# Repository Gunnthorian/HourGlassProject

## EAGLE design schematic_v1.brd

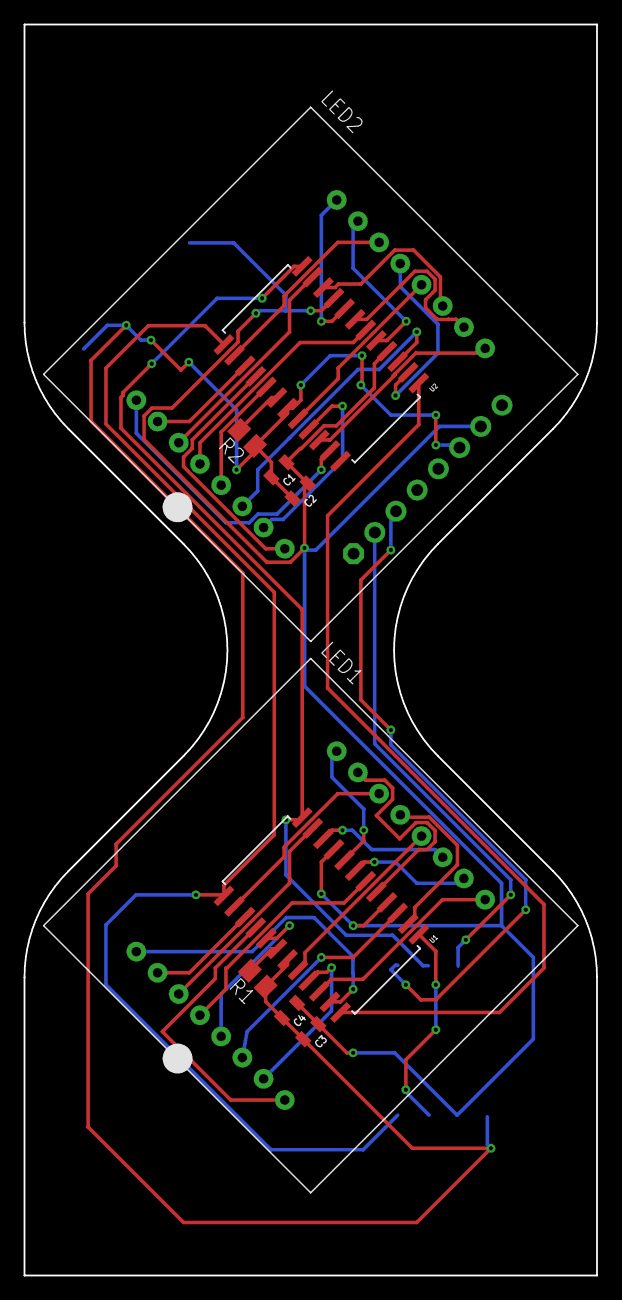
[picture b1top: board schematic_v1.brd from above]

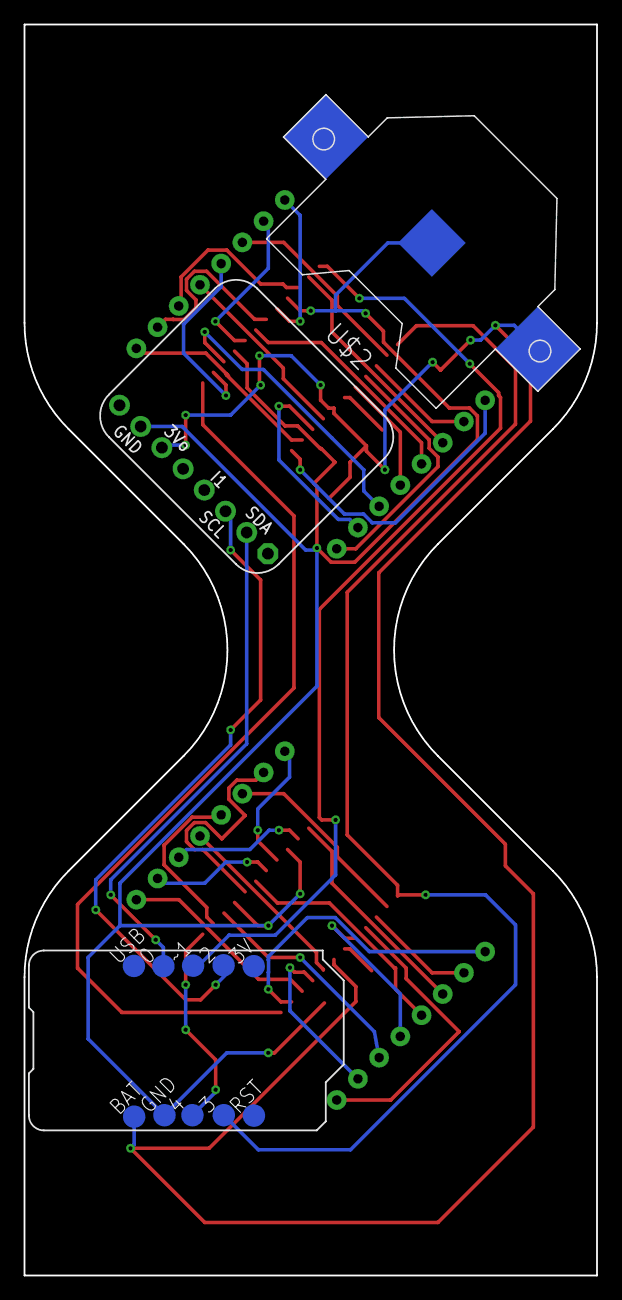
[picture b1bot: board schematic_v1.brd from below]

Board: 2 copper layers, 48.5 x 106.0 mm, 22 parts (11 on the bottom side), 42 nets.

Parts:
0, 2, 3, 3V, 4: TPSQTP19R; TP19R
BAT: TPSQTP19R; TP19R
C1, C2, C3, C4: 10uF; 0805
GND: TPSQTP19R; TP19R
JP1: 1X08_ROUND_70
LED1, LED2: SEGMENT_BL-M12A881UR
R1, R2: 103; M0805
RST: TPSQTP19R; TP19R
U1, U2: MAX7219CWGT; 21-0042B_24
U$2: CR2032-SMD
USB: TPSQTP19R; TP19R
~1: TPSQTP19R; TP19R

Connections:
CLK: 3.TP, U1.13, U2.13
DIN: 4.TP, U1.1
GND: C1.1, C2.1, C3.1, C4.1, GND.TP, JP1.7, U1.4, U1.9, U2.4, U2.9, U$2.-
LOAD: U1.12, U2.12, ~1.TP
unnamed: R2.2, U2.18
unnamed: LED1.13, U1.2
unnamed: LED1.6, U1.3
unnamed: LED1.15, U1.5
unnamed: LED1.4, U1.6
unnamed: LED1.10, U1.7
unnamed: LED1.16, U1.8
unnamed: LED2.13, U2.2
unnamed: LED1.11, U1.10
unnamed: LED1.3, U1.11
unnamed: LED2.6, U2.3
unnamed: LED1.9, U1.22
unnamed: LED1.14, U1.14
unnamed: LED1.8, U1.16
unnamed: LED1.12, U1.20
unnamed: LED1.1, U1.23
unnamed: LED1.7, U1.21
unnamed: LED1.2, U1.15
unnamed: LED1.5, U1.17
unnamed: U1.24, U2.1
unnamed: LED2.15, U2.5
unnamed: LED2.4, U2.6
unnamed: LED2.10, U2.7
unnamed: LED2.16, U2.8
unnamed: LED2.11, U2.10
unnamed: LED2.3, U2.11
unnamed: LED2.9, U2.22
unnamed: LED2.14, U2.14
unnamed: LED2.8, U2.16
unnamed: LED2.12, U2.20
unnamed: LED2.1, U2.23
unnamed: LED2.7, U2.21
unnamed: LED2.2, U2.15
unnamed: LED2.5, U2.17
unnamed: R1.2, U1.18
SCL: 2.TP, JP1.3
SDA: 0.TP, JP1.2
VCC: BAT.TP, C1.2, C2.2, C3.2, C4.2, JP1.6, R1.1, R2.1, U1.19, U2.19, U$2.+$1

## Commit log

2019-01-25 uploading the schematic
2019-01-25 added max7219cwg library
2019-01-25 Added Trinket M0
    Schematic and Board
2019-01-25 Adafrit Trinket M0
2019-01-25 attempting to make max library local
2019-01-25 adding adafruit trinket m0 scematics for reference
2019-01-25 eagle push
2019-02-21 Working on gravity effect.
2019-02-27 big push

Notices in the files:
parts and their libraries:
SparkFun-Capacitors: Licensing: Creative Commons ShareAlike 4.0 International - https://creativecommons.org/licenses/by-sa/4.0
microbuilder: This work is placed in the public domain, and may be freely used for commercial and non-commercial work with the following conditions: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
